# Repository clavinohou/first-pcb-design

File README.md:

# Volume mixer and audio controller (first pcb design) #

## Goals: ##
* Create a pcb
* Music controls
  * Song skip
  * Song play
  * Song pause
* Volume control - though rotary encoder

## Design: ##

Its basically an Arduino Pro Micro just put in the form factor that I wanted. It features 4 MX style contacts for your switches to sit on. There is also a pinout for a rotary encoder for volume adjustment. In the final design I plan to just solder wires to the rotary encoder since the knob I want wont be able to sit right next to the switches. I will make a branch with the code that I eventually use, as well as another branch for the .stl I eventually create, but for now I'm just making sure the circut board actually works.

# Images #

Thanks for looking at my project lmao

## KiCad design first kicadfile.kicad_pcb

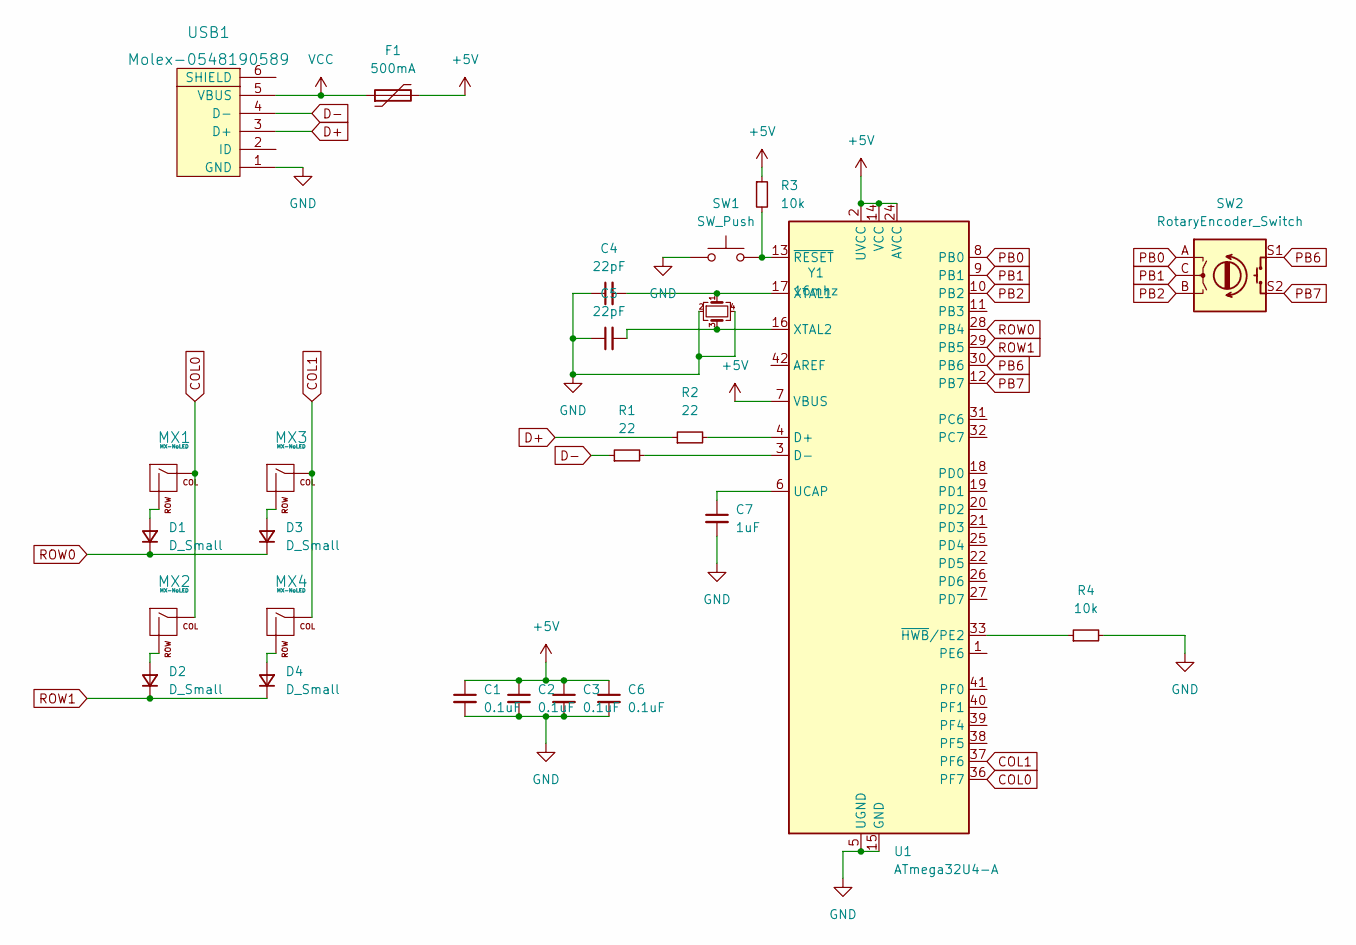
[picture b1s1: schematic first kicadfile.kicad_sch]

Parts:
C1, C2, C3, C6: 0.1uF; C_0805_2012Metric
C4, C5: 22pF; C_0805_2012Metric
C7: 1uF; C_0805_2012Metric
D1, D2, D3, D4: D_Small; D_SOD-123
F1: 500mA; Fuse_1206_3216Metric
MX1, MX2, MX3, MX4: MX-NoLED; MX-1U-NoLED
R1, R2: 22; R_0805_2012Metric
R3, R4: 10k; R_0805_2012Metric
SW1: SW_Push; SKQG-1155865
SW2: RotaryEncoder_Switch; RotaryEncoder_Alps_EC11E-Switch_Vertical_H20mm_CircularMoun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
U1: ATmega32U4-A; TQFP-44_10x10mm_P0.8mm
USB1: Molex-0548190589
Y1: 16mhz; Crystal_SMD_3225-4Pin_3.2x2.5mm

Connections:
+5V: C1.1, C2.1, C3.1, C6.1, F1.2, R3.1, U1.2 (UVCC), U1.7 (VBUS), U1.14 (VCC), U1.24 (AVCC), U1.34 (VCC), U1.44 (AVCC)
COL0: MX1.1 (COL), MX2.1 (COL), U1.36 (PF7)
COL1: MX3.1 (COL), MX4.1 (COL), U1.37 (PF6)
D+: R2.1, USB1.3 (D+)
D-: R1.1, USB1.4 (D-)
GND: C1.2, C2.2, C3.2, C4.1, C5.1, C6.2, C7.2, R4.2, SW1.1, U1.5 (UGND), U1.15 (GND), U1.23 (GND), U1.35 (GND), U1.43 (GND), USB1.1 (GND), Y1.2, Y1.4
unnamed: C4.2, U1.17 (XTAL1), Y1.1
unnamed: C5.2, U1.16 (XTAL2), Y1.3
unnamed: C7.1, U1.6 (UCAP)
unnamed: D1.2 (A), MX1.2 (ROW)
unnamed: D2.2 (A), MX2.2 (ROW)
unnamed: D3.2 (A), MX3.2 (ROW)
unnamed: D4.2 (A), MX4.2 (ROW)
unnamed: R1.2, U1.3 (D-)
unnamed: R2.2, U1.4 (D+)
unnamed: R3.2, SW1.2, U1.13 (~RESET)
unnamed: R4.1, U1.33 (~HWB/PE2)
PB0: SW2.A, U1.8 (PB0)
PB1: SW2.C, U1.9 (PB1)
PB2: SW2.B, U1.10 (PB2)
PB6: SW2.S1, U1.30 (PB6)
PB7: SW2.S2, U1.12 (PB7)
ROW0: D1.1 (K), D3.1 (K), U1.28 (PB4)
ROW1: D2.1 (K), D4.1 (K), U1.29 (PB5)
VCC: F1.1, USB1.5 (VBUS)

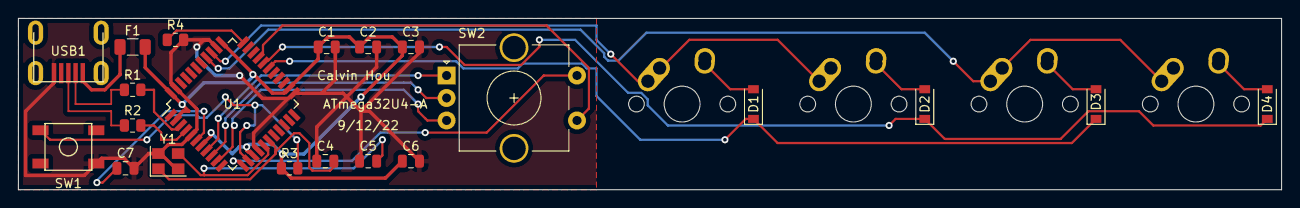
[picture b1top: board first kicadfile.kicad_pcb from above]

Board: 2 copper layers, 140.5 x 19.1 mm, 25 parts (0 on the bottom side), 25 nets.

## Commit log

2022-09-08 initialization
    created files and stuff!
2022-09-08 finished setup
    big win
2022-09-08 finished mcu schematicx
2022-11-04 Final version
    lol i forgot to use github but this should be all the kicad files i used, as well as the final gerber and cut files
